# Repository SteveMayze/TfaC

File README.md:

# TfaC
Time for a Change is a project to give new life to an old alarm clock.

Originally stated in https://smayze.wordpress.com/2015/05/05/time-for-a-change.
The purpose of this project is to provide a facility to learn about micro-controller
interfacing with other components using a practical example. At the same time, SysML
will be used to model the project in an attempt to also learn the application of
SysML.

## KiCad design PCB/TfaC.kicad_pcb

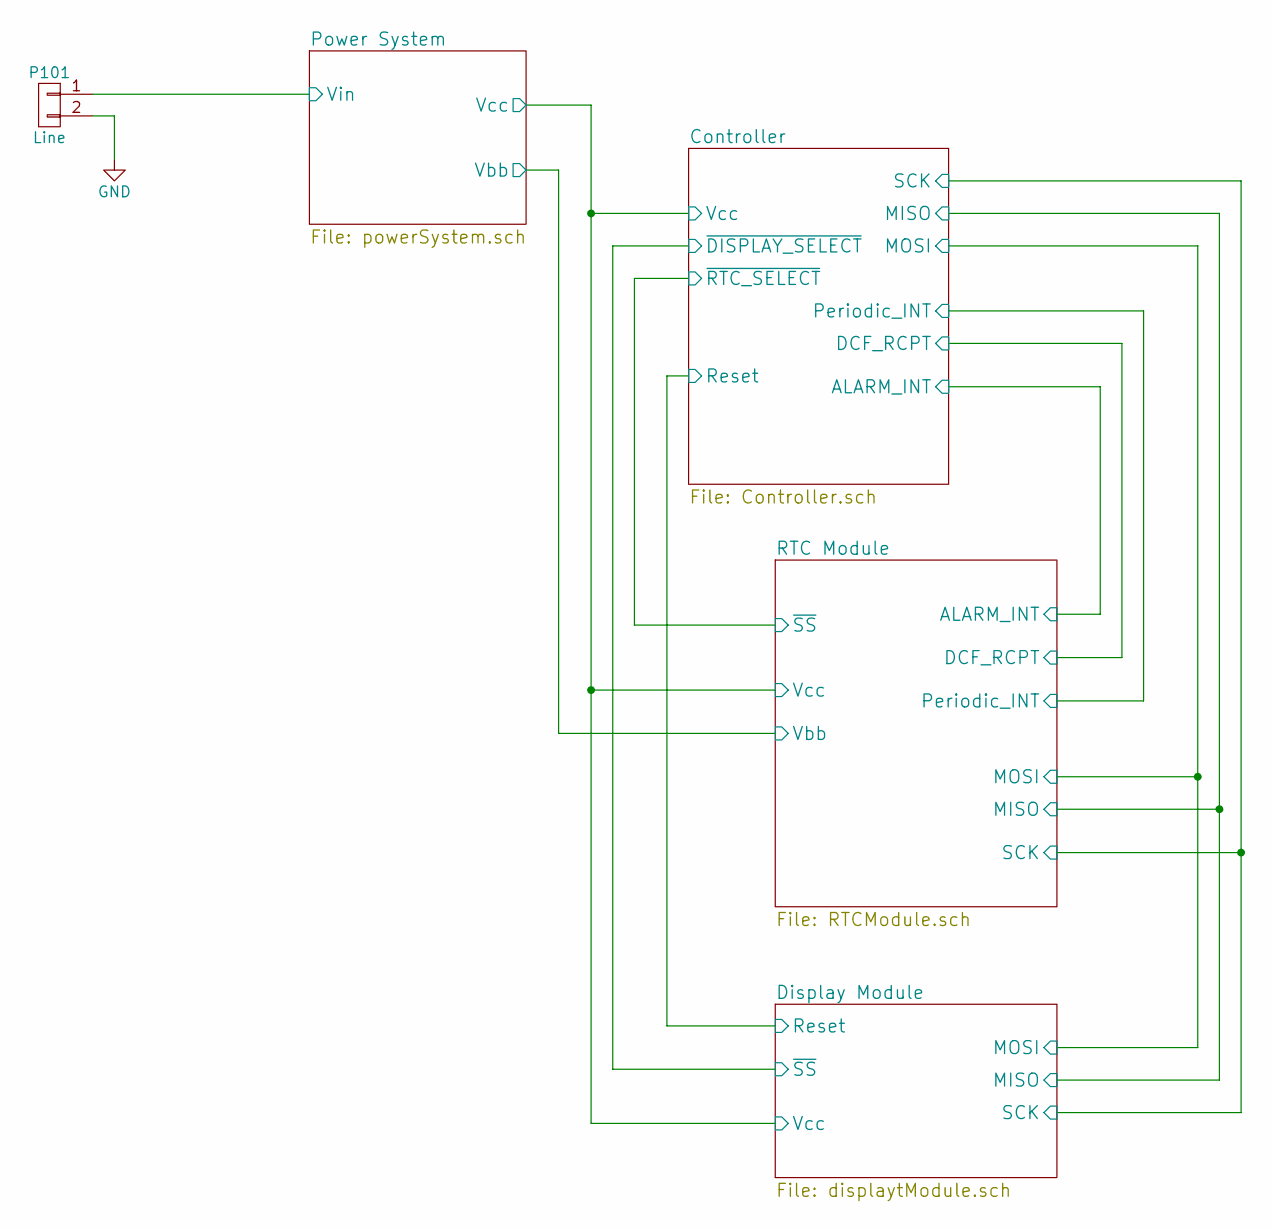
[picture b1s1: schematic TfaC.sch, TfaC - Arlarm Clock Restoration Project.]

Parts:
P101: Line; Pin_Header_Straight_1x02

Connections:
/Power System/Vin: P101.1; also elsewhere on the board
GND: P101.2; also elsewhere on the board

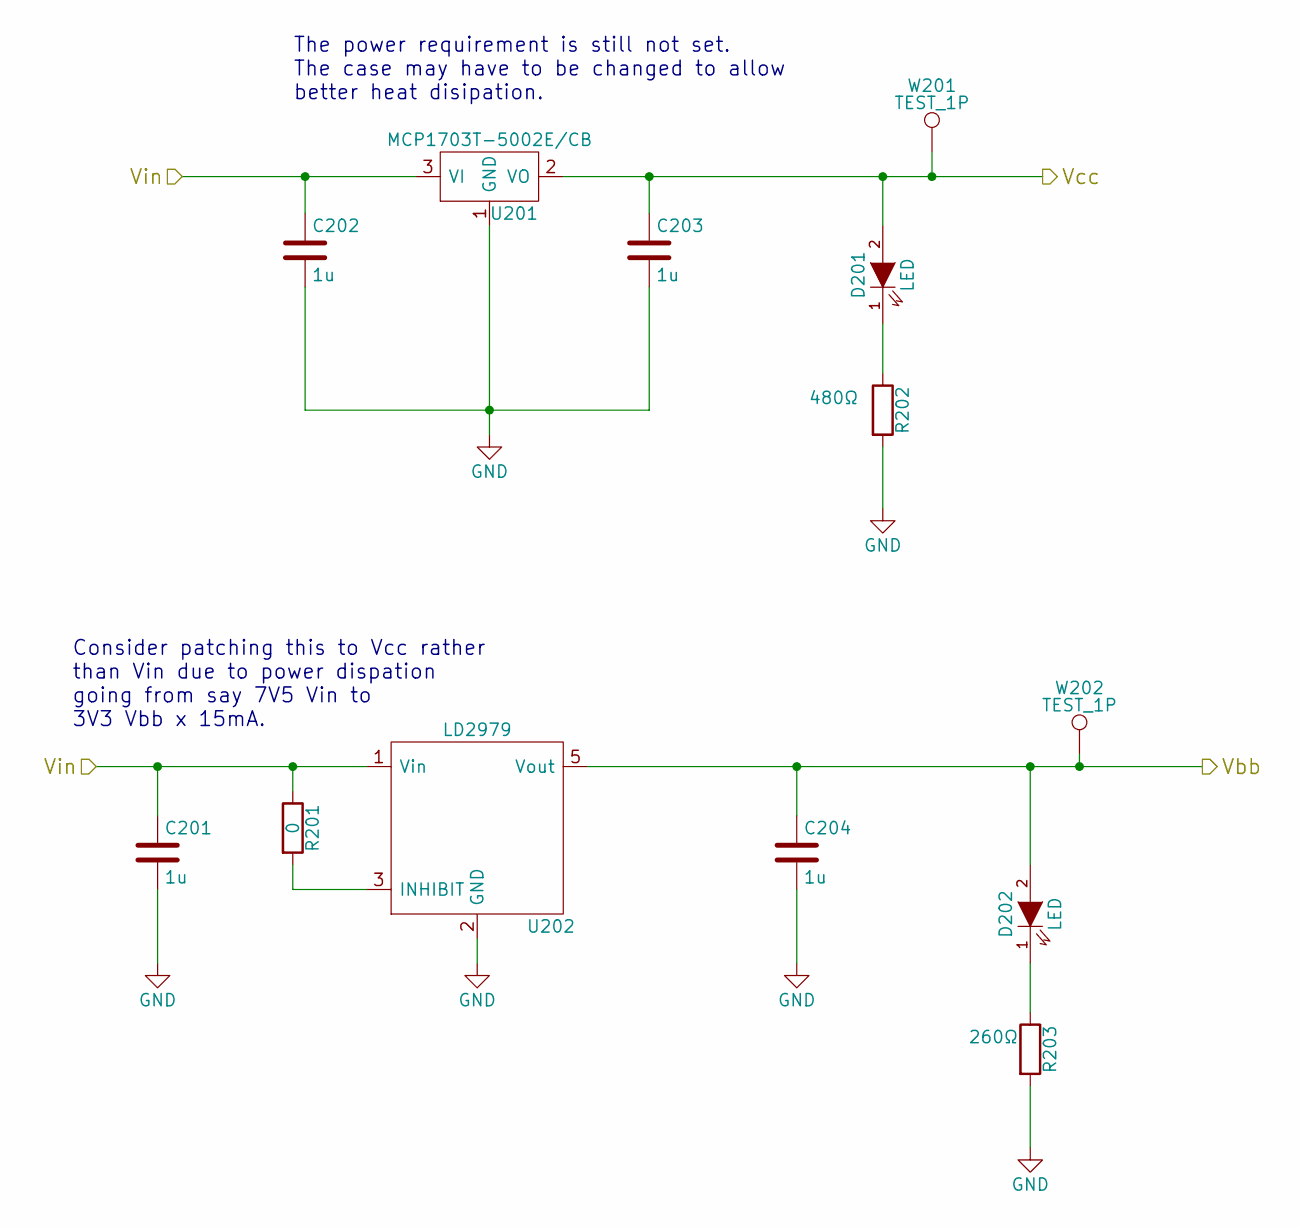
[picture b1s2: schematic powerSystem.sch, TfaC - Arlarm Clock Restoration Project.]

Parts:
C201, C203, C204: 1u; C_0805_HandSoldering
C202: 1u; C_0805_HandSoldering; MPN Value
D201, D202: LED; LED_0805
R201: 0; R_0805_HandSoldering
R202: 480Ω; R_0805_HandSoldering
R203: 260Ω; R_0805_HandSoldering
U201: MCP1703T-5002E/CB; SOT-23A; MPN MCP1703T-5002E/CB
U202: LD2979; SOT-23-5L
W201, W202: TEST_1P; Measurement_Point_Round-SMD-Pad_Small

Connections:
/Controller/Vcc: C203.1, D201.2 (A), U201.2 (VO), W201.1; also elsewhere on the board
/Power System/Vbb: C204.1, D202.2 (A), U202.5 (Vout), W202.1; also elsewhere on the board
/Power System/Vin: C201.1, C202.1, R201.1, U201.3 (VI), U202.1 (Vin); also elsewhere on the board
GND: C201.2, C202.2, C203.2, C204.2, R202.2, R203.2, U201.1 (GND), U202.2 (GND); also elsewhere on the board
unnamed: D201.1 (K), R202.1
unnamed: D202.1 (K), R203.1
unnamed: R201.2, U202.3 (INHIBIT)

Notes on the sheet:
Consider patching this to Vcc rather than Vin due to power dispation going from say 7V5 Vin to 3V3 Vbb x 15mA.
The power requirement is still not set. The case may have to be changed to allow better heat disipation.

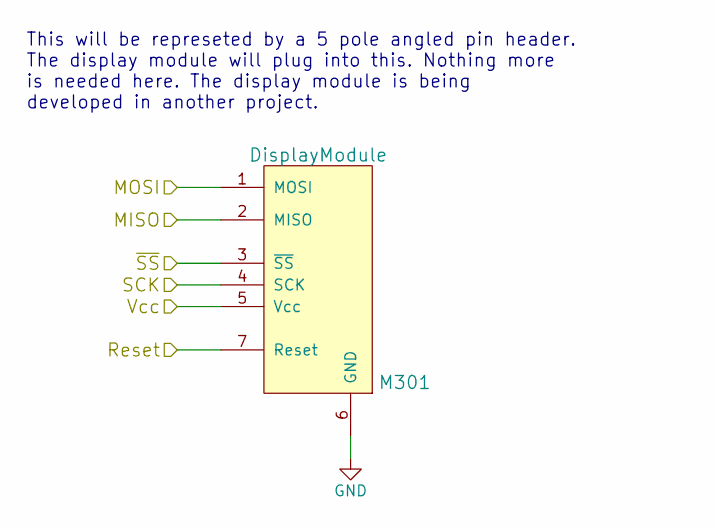
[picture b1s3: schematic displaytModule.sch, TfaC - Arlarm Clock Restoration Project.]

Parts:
M301: DisplayModule; Pin_Header_Straight_1x07

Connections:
/Controller/MISO: M301.2 (MISO); also elsewhere on the board
/Controller/MOSI: M301.1 (MOSI); also elsewhere on the board
/Controller/Reset: M301.7 (Reset); also elsewhere on the board
/Controller/SCK: M301.4 (SCK); also elsewhere on the board
/Controller/Vcc: M301.5 (Vcc); also elsewhere on the board
/Controller/~DISPLAY_SELECT: M301.3 (~SS); also elsewhere on the board
GND: M301.6 (GND); also elsewhere on the board

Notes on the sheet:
This will be represeted by a 5 pole angled pin header. The display module will plug into this. Nothing more is needed here. The display module is being developed in another project.

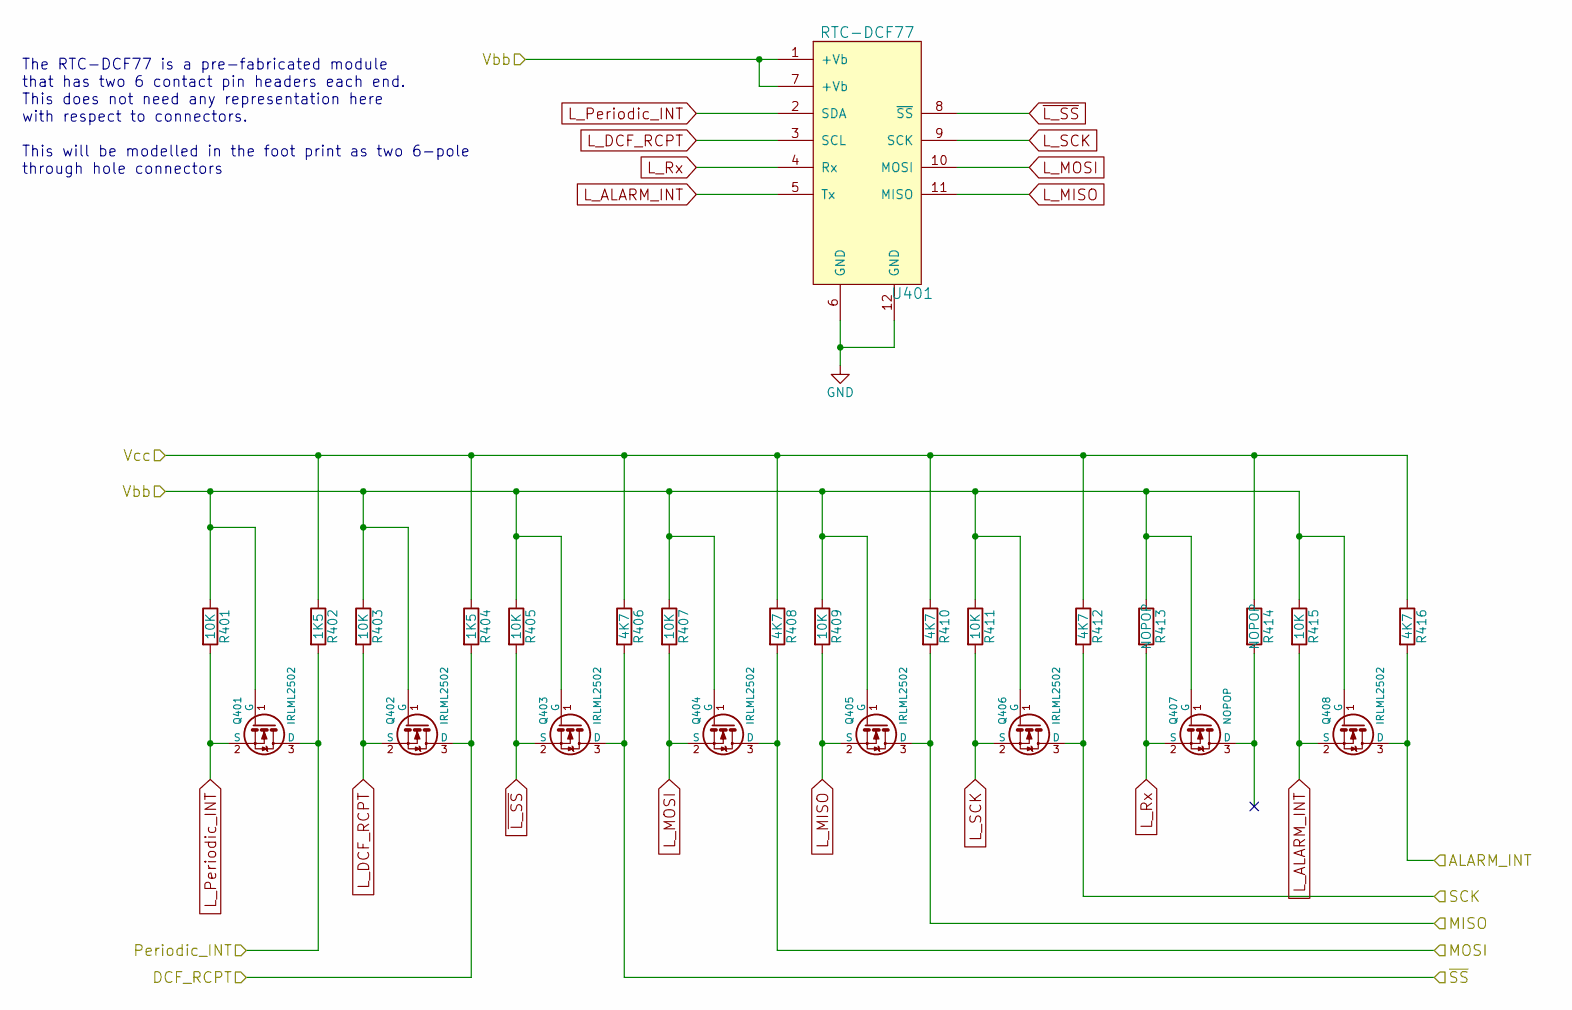
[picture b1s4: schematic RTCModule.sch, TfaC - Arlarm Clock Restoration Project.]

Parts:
Q401, Q402, Q403, Q404, Q405, Q406, Q408: IRLML2502; Micro3
Q407: NOPOP; Micro3
R401, R403, R405, R407, R409, R411, R415: 10K; R_0805_HandSoldering
R402, R404: 1K5; R_0805_HandSoldering
R406, R408, R410, R412, R416: 4K7; R_0805_HandSoldering
R413, R414: NOPOP; R_0805_HandSoldering
U401: RTC-DCF77; RTC-DCF

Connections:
/Controller/ALARM_INT: Q408.3 (D), R416.2; also elsewhere on the board
/Controller/DCF_RCPT: Q402.3 (D), R404.2; also elsewhere on the board
/Controller/MISO: Q405.3 (D), R410.2; also elsewhere on the board
/Controller/MOSI: Q404.3 (D), R408.2; also elsewhere on the board
/Controller/Periodic_INT: Q401.3 (D), R402.2; also elsewhere on the board
/Controller/SCK: Q406.3 (D), R412.2; also elsewhere on the board
/Controller/Vcc: R402.1, R404.1, R406.1, R408.1, R410.1, R412.1, R414.1, R416.1; also elsewhere on the board
/Controller/~RTC_SELECT: Q403.3 (D), R406.2; also elsewhere on the board
/Power System/Vbb: Q401.1 (G), Q402.1 (G), Q403.1 (G), Q404.1 (G), Q405.1 (G), Q406.1 (G), Q407.1 (G), Q408.1 (G), R401.1, R403.1, R405.1, R407.1, R409.1, R411.1, R413.1, R415.1, U401.1 (+Vb), U401.7 (+Vb); also elsewhere on the board
GND: U401.6 (GND), U401.12 (GND); also elsewhere on the board
L_ALARM_INT: Q408.2 (S), R415.2, U401.5 (Tx)
L_DCF_RCPT: Q402.2 (S), R403.2, U401.3 (SCL)
L_MISO: Q405.2 (S), R409.2, U401.11 (MISO)
L_MOSI: Q404.2 (S), R407.2, U401.10 (MOSI)
L_Periodic_INT: Q401.2 (S), R401.2, U401.2 (SDA)
L_Rx: Q407.2 (S), R413.2, U401.4 (Rx)
L_SCK: Q406.2 (S), R411.2, U401.9 (SCK)
unnamed: Q407.3 (D), R414.2
~L_SS: Q403.2 (S), R405.2, U401.8 (~SS)

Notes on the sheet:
The RTC-DCF77 is a pre-fabricated module that has two 6 contact pin headers each end. This does not need any representation here with respect to connectors. This will be modelled in the foot print as two 6-pole through hole connectors

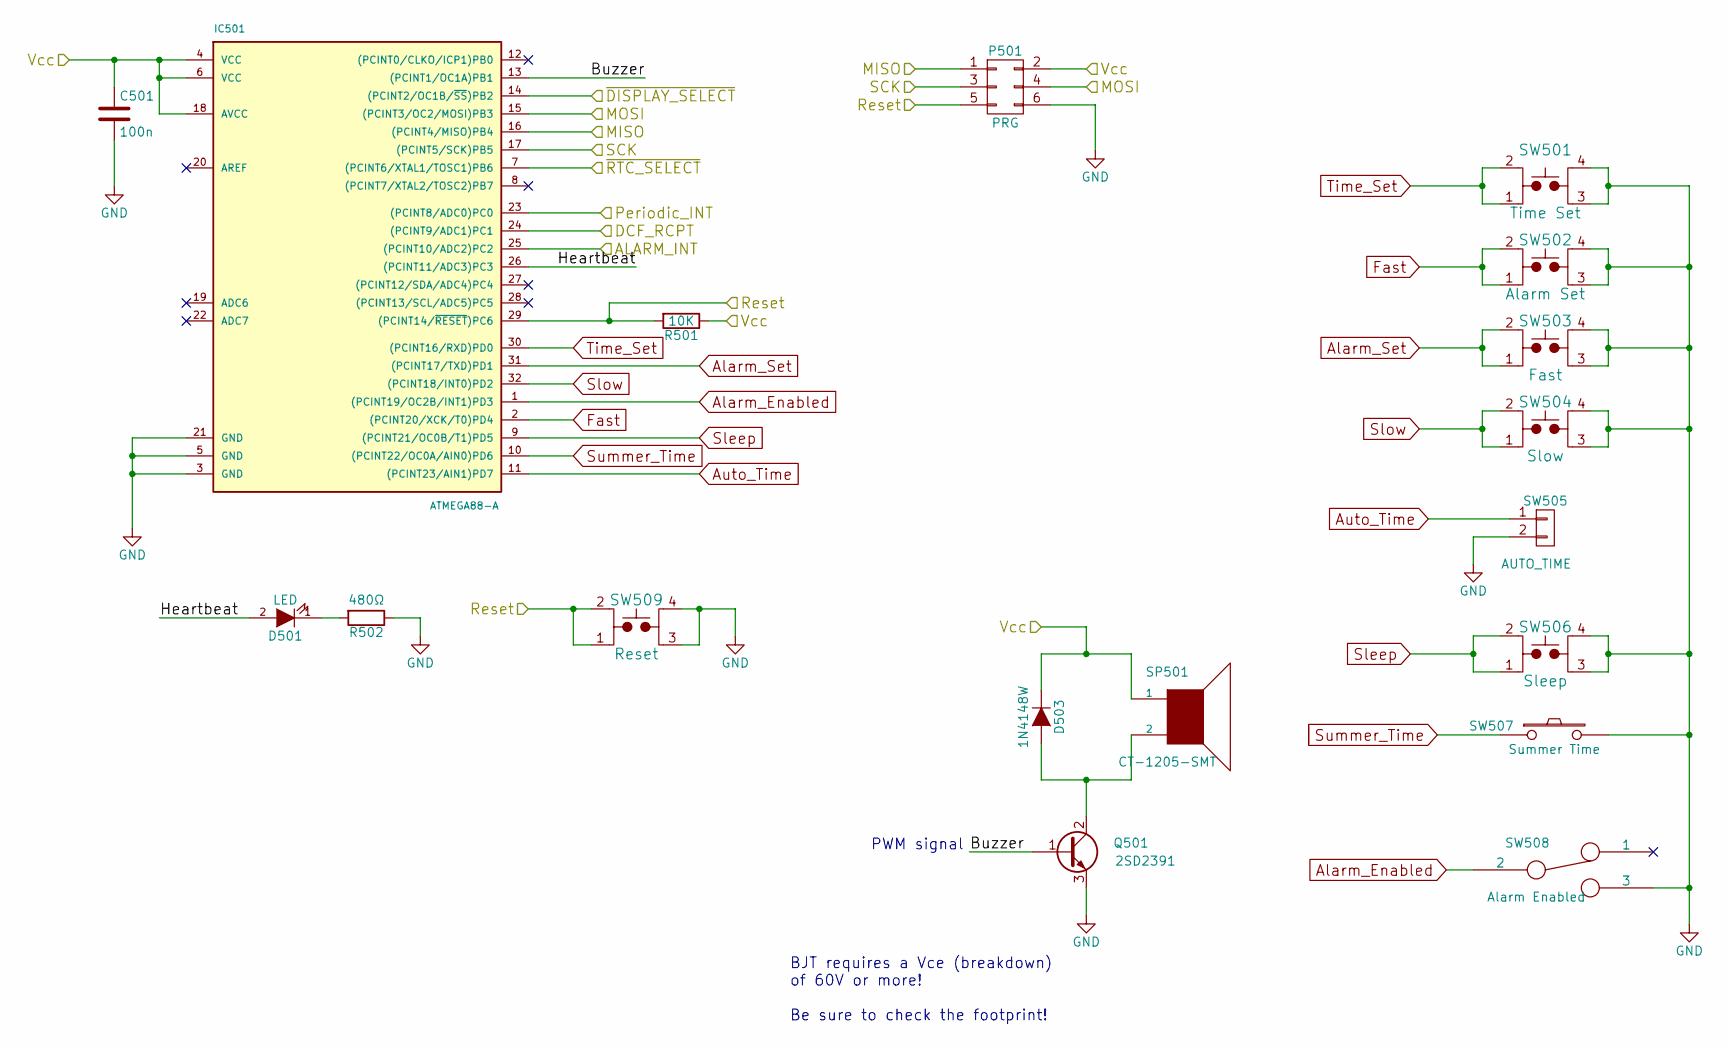
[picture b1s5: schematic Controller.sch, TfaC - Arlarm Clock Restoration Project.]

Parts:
C501: 100n; C_0805_HandSoldering
D501: LED; LED_0805; Voltage Value; DigiKeyPN Value
D503: 1N4148W; SOD-123; Voltage Value; DigiKeyPN Value
IC501: ATMEGA88-A; LQFP-32_7x7mm_Pitch0.8mm
P501: PRG; Pin_Header_Straight_2x03
Q501: 2SD2391; SOT89-3_Housing; Voltage Value; DigiKeyPN Value
R501: 10K; R_0805_HandSoldering
R502: 480Ω; R_0805_HandSoldering
SP501: CT-1205-SMT; Voltage Value; DigiKeyPN 102-1199-2-ND
SW501: Time Set; TL3315; MPN Value
SW502: Alarm Set; TL3315
SW503: Fast; TL3315
SW504: Slow; TL3315
SW505: AUTO_TIME; Pin_Header_Straight_1x02
SW506: Sleep; TL3315
SW507: Summer Time; Pin_Header_Straight_1x02
SW508: Alarm Enabled; CLSB12C01
SW509: Reset; PTS525SM15SMTR2LFS

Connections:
/Controller/ALARM_INT: IC501.25 ((PCINT10/ADC2)PC2); also elsewhere on the board
/Controller/Buzzer: IC501.13 ((PCINT1/OC1A)PB1), Q501.1 (B)
/Controller/DCF_RCPT: IC501.24 ((PCINT9/ADC1)PC1); also elsewhere on the board
/Controller/Heartbeat: D501.2 (A), IC501.26 ((PCINT11/ADC3)PC3)
/Controller/MISO: IC501.16 ((PCINT4/MISO)PB4), P501.1; also elsewhere on the board
/Controller/MOSI: IC501.15 ((PCINT3/OC2/MOSI)PB3), P501.4; also elsewhere on the board
/Controller/Periodic_INT: IC501.23 ((PCINT8/ADC0)PC0); also elsewhere on the board
/Controller/Reset: IC501.29 ((PCINT14/~RESET~)PC6), P501.5, R501.2, SW509.1, SW509.2; also elsewhere on the board
/Controller/SCK: IC501.17 ((PCINT5/SCK)PB5), P501.3; also elsewhere on the board
/Controller/Vcc: C501.1, D503.1 (K), IC501.4 (VCC), IC501.6 (VCC), IC501.18 (AVCC), P501.2, R501.1, SP501.1; also elsewhere on the board
/Controller/~DISPLAY_SELECT: IC501.14 ((PCINT2/OC1B/~SS~)PB2); also elsewhere on the board
/Controller/~RTC_SELECT: IC501.7 ((PCINT6/XTAL1/TOSC1)PB6); also elsewhere on the board
Alarm_Enabled: IC501.1 ((PCINT19/OC2B/INT1)PD3), SW508.2
Alarm_Set: IC501.31 ((PCINT17/TXD)PD1), SW503.1, SW503.2
Auto_Time: IC501.11 ((PCINT23/AIN1)PD7), SW505.1
Fast: IC501.2 ((PCINT20/XCK/T0)PD4), SW502.1, SW502.2
GND: C501.2, IC501.3 (GND), IC501.5 (GND), IC501.21 (GND), P501.6, Q501.3 (E), R502.1, SW501.3, SW501.4, SW502.3, SW502.4, SW503.3, SW503.4, SW504.3, SW504.4, SW505.2, SW506.3, SW506.4, SW507.2, SW508.3, SW509.3, SW509.4; also elsewhere on the board
unnamed: D501.1 (K), R502.2
unnamed: D503.2 (A), Q501.2 (C), SP501.2
Sleep: IC501.9 ((PCINT21/OC0B/T1)PD5), SW506.1, SW506.2
Slow: IC501.32 ((PCINT18/INT0)PD2), SW504.1, SW504.2
Summer_Time: IC501.10 ((PCINT22/OC0A/AIN0)PD6), SW507.1
Time_Set: IC501.30 ((PCINT16/RXD)PD0), SW501.1, SW501.2

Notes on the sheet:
BJT requires a Vce (breakdown) of 60V or more! Be sure to check the footprint!
PWM signal

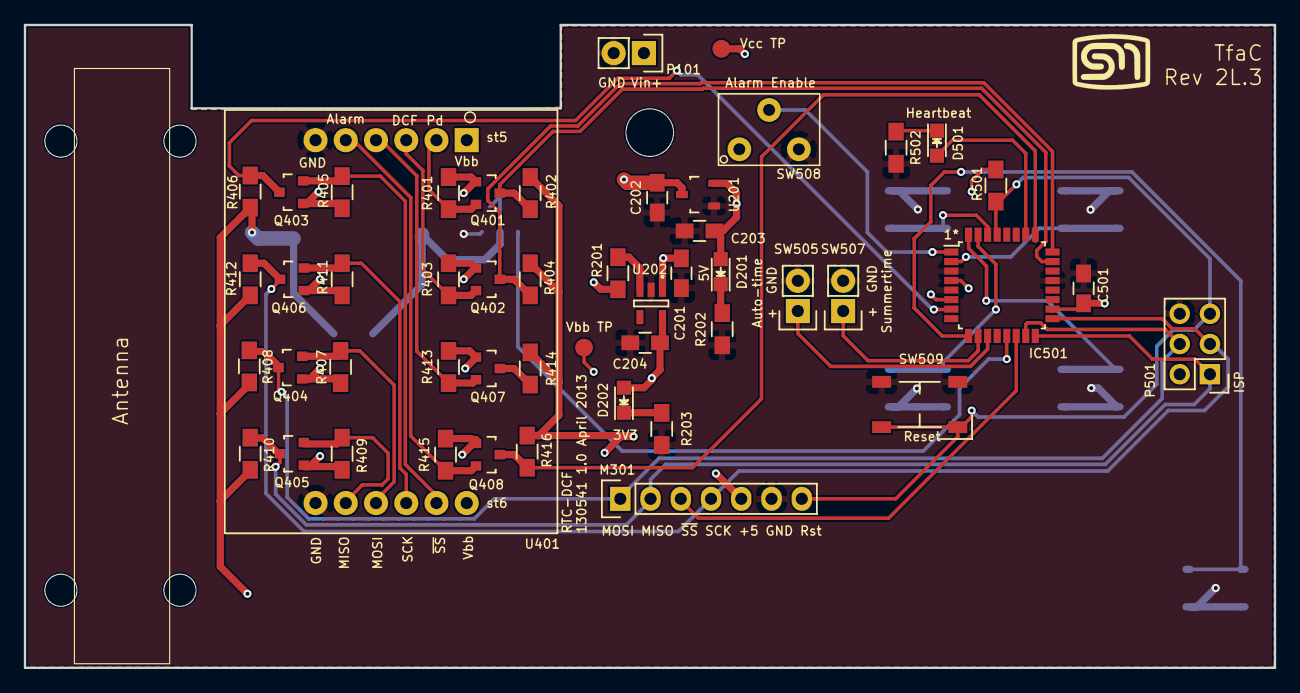
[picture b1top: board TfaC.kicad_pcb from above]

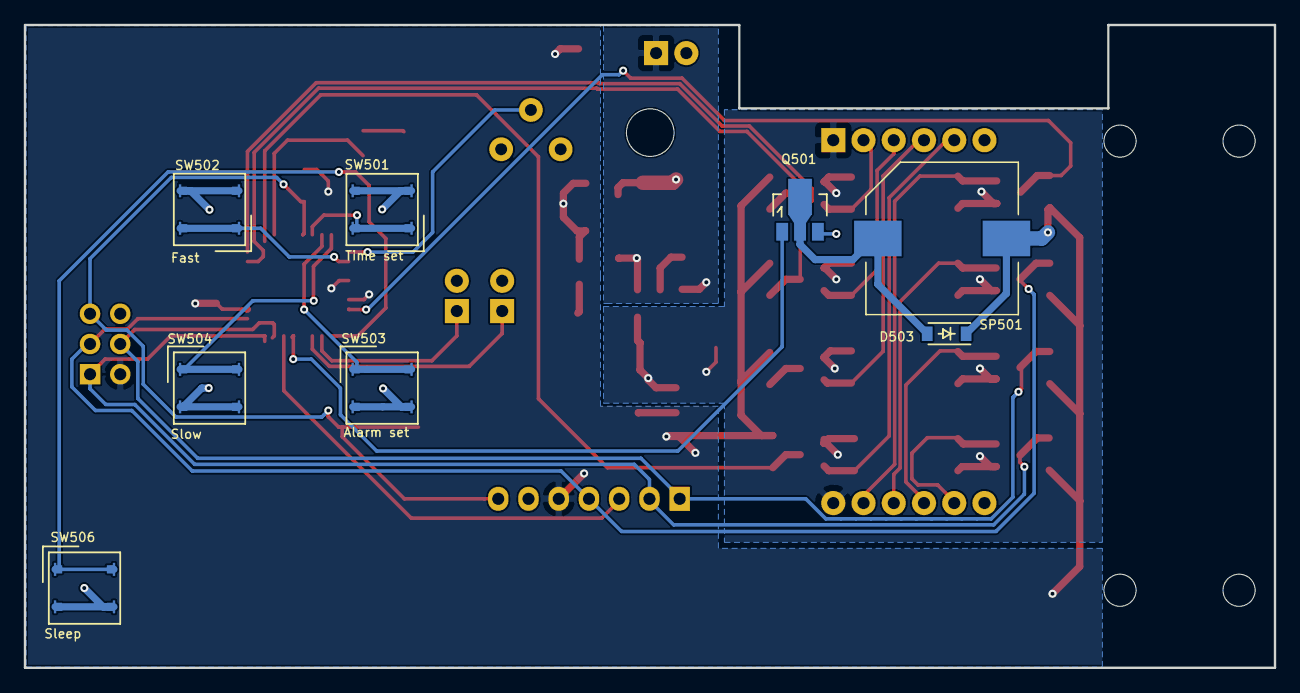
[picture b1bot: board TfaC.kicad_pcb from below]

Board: 2 copper layers, 105.0 x 54.0 mm, 59 parts (8 on the bottom side), 37 nets.

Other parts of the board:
MNT1: MountingHole_4mm

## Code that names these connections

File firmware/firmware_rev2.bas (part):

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' Time set etc. buttons ...........
Ddrd = &B10000000
Portd = &B01111111
Time_set Alias Pind.0
Fast_set Alias Pind.4
Slow_set Alias Pind.2
Alarm_switch Alias Pind.3
Alarm_set Alias Pind.1
Sleep_btn Alias Pind.5
Summertime Alias Pind.6


Heartbeat Alias Portb.0
Config Heartbeat = Output : Heartbeat = 0
Btn_ack Alias Portb.6                                       ' Temporary output
Config Btn_ack = Output : Btn_ack = 0

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Dim Dfc_time As Byte
Dfc_time = 250
Dim Periodic_int As Bit
Periodic_int = 0

Dim Btn_interrupt_fired As Bit
Btn_interrupt_fired = 0
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
   If Rtc_interrupt_fired = 1 Then
      If Periodic_int = 1 Then
         Periodic_int = 0
         If Alarmdisplay = 1 Then
            Set Btn_ack
            Display_time(seconds_i) = Makebcd(alarm_seconds)
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
Pcint1_isr:
   Rtc_interrupt_fired = 1
   If Second_interrupt = 0 Then Periodic_int = 1
   If Dfc_interrupt = 0 Then Dfc_time = 0
Return

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
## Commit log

2015-05-16 Initial check in for the EA repository
2015-05-17 Added user cases and basic paths
2015-05-19 Filled in more of the clock IBB
    The internal block diagram for the clock has been fleshed out a bit more
    along with the definitions for the other, dependant blocks.
2015-05-23 Updated the internal block diagram for the clock system
2015-05-23 Added state machine for the clock system
2015-05-23 Initial checkin of the kicad schematic hierachry
2015-05-27 Started the schematic. Added the power circuit
2015-06-01 Corrected symbol for the LD2979 and filtering capacitors
2015-06-01 Added spice model to explore the use of a voltage divider
2015-06-04 Updated the schematic for the RTC and controller
2015-06-06 Coloured the RTC symbol for presentation
2015-06-06 Updated the main block diagram
    New findings during the schematic have been updated into the SysML
    model.
2015-06-10 Created the display module block diagram
2015-06-10 Added 7 segment data sheet
2015-06-10 Added alternate display module block diagram
2015-06-10 Screenshots
2015-07-04 Added some images
2015-07-04 Added the symbol for the display module, which will actually be just a pin header
2015-07-12 correction to the reset circuit
2015-07-12 Initial main board PCB outline
2015-07-13 Update to the model
2015-08-04 Generated the Netlist and started associating footprints
2015-08-04 Updated some docs for switches
2015-08-04 Added a document for reference
2015-08-16 Added the tactile switch
2015-08-16 Added the switch footprints and started the layout
2015-08-16 Added some datasheets etc
2015-08-19 Started the layout
2015-08-23 Getting up to date
2015-09-08 Added a couple of images to document the progress (for the display module)
2015-09-10 Added isolation resistors and corrected the reset connection
2015-09-10 Corrected isolation resistor from 4.7k to 1k
2015-09-20 Trying out an alternative layout
2015-09-22 Completed draft layout for the alternate layout
2015-09-22 Completed the layout and generated the Gerbers
2015-10-13 2L.2 board corrections
2015-10-27 Made corrections to the board for rev 2L.2
2015-10-27 Touched up some routs to avoid zone borders
2015-10-27 Created gerbers for TfaC-Rev 2L.2.a2f0245
2015-10-27 Started on the main board firmware
2015-11-06 small changes
2015-11-18 Firmware changes
2015-11-19 Added indicator LEDs and Heartbeat
2015-11-19 Created a prototype firmware for SPI using MyAVR
2015-11-29 Updted the prototype firmware for further testing
2015-12-03 Updated the firmware to work with SPI RTC and display
2015-12-03 Updated the board for further features to the display
2015-12-03 Updated revision number
2015-12-10 Working model of the firmware using the micro based display
2015-12-12 Removed the kicad cache from the .gitignore
2015-12-12 Corrected the symbol and footprint for the reset switch
2015-12-12 Added the missing track for the reset switch with the new foot print
2015-12-13 Disabled the interrupts when accessing the SPI
2015-12-15 intermediate checkin of firmware_rev1.bas to mark a potential candidate
2015-12-31 An intermediate save of code that is basically working
2015-12-31 Removed the csv files... to big
2015-12-31 Register addresses for the micro ctrl display must have bit 7 set. Images for Blog also added
2016-01-03 firmware/firmware_rev1.bas that works with a high percent of precision 0.03% failure
2016-01-04 Cleaned up the conversion of BCD and Decimal that are not required and clened up other unused variables
2016-01-16 Updated the model to bring it in line with the current state of the prototype findings
2016-01-18 Updated the model a bit more
2016-01-24 Added stress test to check the display
2016-01-24 Updated the model with more detail to the blocks
2016-01-30 Updated the block diagram with the Port C PCINT
    Port C is going to be used for the UI i.e. the control switches for the
    alarm clock such as alarm set, time set etc. The block diagram was
    updated to highlight the PCINT numbers for the input pins.
2016-02-09 A new stress test
2016-02-09 Added button handling for setting the alarm values
    Corrected the issue where the fast-set and alarm-set buttons are
    swapped!
2016-02-16 Added rev3 of the firmware for the alarm
2016-03-08 Updated the routing to comply with the display module
2016-03-08 Shifted the ISP to a more sensible location
2016-03-09 Cleaned up some more routes
2016-04-25 Added alarm
2016-05-10 Created firmware_rev4 to use one of the indicators as the DCF Received lamp
2016-05-10 stopped using the indicator on the main board and only on the display for the DFC signal received
2016-07-28 Re-organised the board to incorporate the MISO
2016-07-31 Revision 2L_3 Gerbers and sent to OSHPark
2016-09-01 Updated the heartbeat output in preperation for the buzzer
2016-10-11 Firmware_rev5: Able to get the alarm to fire by reading the status register
2016-10-12 firmware_rev6: Cleaned up the operation and the alarm enable feature
2016-10-13 firmware_rev7: delay for main board start up to give time for the display
2016-10-13 firmware_rev7: Initialisation and alaram cancel
2016-10-13 firmware_rev7: improved the performance of the alarm setting buttons
2016-10-15 firmware_rev7: Fixed the initial time when the alarm is disabled
2016-10-15 firmware_rev7: fixed alarm not ending correctly
2016-10-16 firmware_rev7: Padded out the start up to give time for the RTC-DFC
2016-10-16 Started BOM analysis
2016-10-16 Added diagram notes
2016-10-16 re-created the BOM for analysis
2016-10-16 firmware_rev7 comment changes
2016-10-16 Updated the BOM for the cust analysis
2016-10-16 BOM Added the cost of the boards
2017-10-21 Updates to the alarm handling
